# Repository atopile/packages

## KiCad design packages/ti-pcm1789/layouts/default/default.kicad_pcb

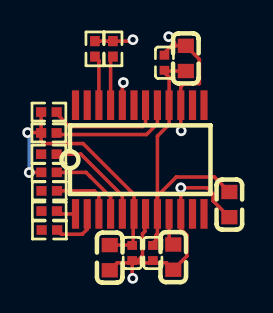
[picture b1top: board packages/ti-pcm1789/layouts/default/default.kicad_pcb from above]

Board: 2 copper layers, 17 parts (0 on the bottom side), 13 nets.

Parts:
C1, C2, C3: 1e-06F; C0402
C4, C5, C6, C7: 9.999F; C0603
R1, R6, R7, R8, R9: 10000Ω; R0402
R2, R3, R4, R5: 22Ω; R0402
U1: TSSOP-24_L7.8-W4.4-P0.65-LS6.4-BL

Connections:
AMUTEI: R6.1, U1.17
BCK: R4.2, U1.2
DIN: R2.2, U1.3
LRCK: R3.2, U1.1
RST: R1.1, U1.4
SCKI: R5.2, U1.5
SCL: R8.1, U1.22
SDA: R9.1, U1.21
ZERO2_AMUTEO: R7.1, U1.18
decoupling_1uf[0]-power-hv: C1.1, C4.1, R1.2, R6.2, R7.2, R8.2, R9.2, U1.6
decoupling_1uf[2]-power-hv: C2.1, C3.1, C5.1, C6.1, U1.8, U1.16
hv: C7.1, U1.9
lv: C1.2, C2.2, C3.2, C4.2, C5.2, C6.2, C7.2, U1.7, U1.10, U1.15, U1.20, U1.23, U1.24

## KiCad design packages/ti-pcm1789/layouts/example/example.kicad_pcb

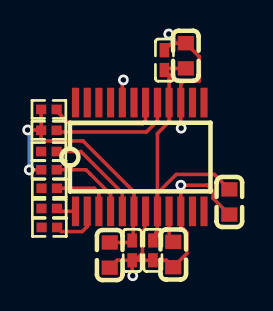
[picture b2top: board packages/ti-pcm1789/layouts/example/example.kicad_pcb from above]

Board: 2 copper layers, 15 parts (0 on the bottom side), 11 nets.

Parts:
C1, C2, C3: 1µF ±10% 25V X5R; C0402
C4, C5, C6, C7: 10µF ±10% 10V X5R; C0603
R1, R2, R3, R4: 22Ω ±1% 62.5mW; R0402
R5, R6, R7: 10kΩ ±1% 62.5mW; R0402
U1: TSSOP-24_L7.8-W4.4-P0.65-LS6.4-BL

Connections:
AMUTEI: R5.1, U1.17
BCK: R3.2, U1.2
DIN: R1.2, U1.3
LRCK: R2.2, U1.1
RST: R6.1, U1.4
SCKI: R4.2, U1.5
VCOM: C7.1, U1.9
ZERO2_AMUTEO: R7.1, U1.18
gnd: C1.2, C2.2, C3.2, C4.2, C5.2, C6.2, C7.2, U1.7, U1.10, U1.15, U1.20
hv: C1.1, C4.1, R5.2, R6.2, R7.2, U1.6
hv-1: C2.1, C3.1, C5.1, C6.1, U1.8, U1.16

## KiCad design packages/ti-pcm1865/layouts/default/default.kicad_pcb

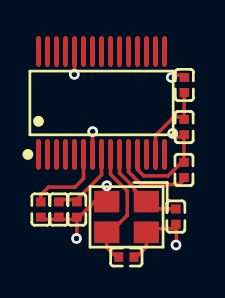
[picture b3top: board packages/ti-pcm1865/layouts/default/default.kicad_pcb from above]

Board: 2 copper layers, 10 parts (0 on the bottom side), 6 nets.

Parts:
C1, C5: 9.999F; C0402
C2, C6: 1F; C0402
C3, C4: 1.2e-F; C0402
C7, C8: 2.2e-F; C0402
U1: TSSOP-30_L7.8-W4.4-P0.50-LS6.4-BL
X1: CRYSTAL-SMD_4P-L3.2-W2.5-BL

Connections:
_power_ldo_cap-power-hv: C7.1, U1.11
_vref_cap-power-hv: C8.1, U1.6
crystal_caps[0]-power-hv: C3.1, U1.10, X1.1
crystal_caps[1]-power-hv: C4.1, U1.9, X1.3
hv: C1.1, C2.1, C5.1, C6.1, U1.8, U1.13, U1.14
lv: C1.2, C2.2, C3.2, C4.2, C5.2, C6.2, C7.2, C8.2, U1.7, U1.12, U1.25, U1.26, X1.2, X1.4

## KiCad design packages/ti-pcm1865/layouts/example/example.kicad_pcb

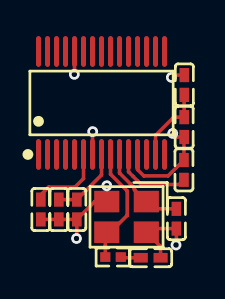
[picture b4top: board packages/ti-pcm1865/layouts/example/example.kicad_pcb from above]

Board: 2 copper layers, 11 parts (0 on the bottom side), 7 nets.

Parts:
C1, C8: 2.2µF ±20% 6.3V X5R; C0402
C2, C6: 10µF ±20% 6.3V X5R; C0402
C3, C7: 100nF ±10% 16V X7R; C0402
C4, C5: 15pF ±5% 50V C0G; C0402
R1: 0Ω 62.5mW; R0402
U1: TSSOP-30_L7.8-W4.4-P0.50-LS6.4-BL
X1: CRYSTAL-SMD_4P-L3.2-W2.5-BL

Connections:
LDO: C1.1, U1.11
VREF: C8.1, U1.6
XI: C5.1, U1.10, X1.1
XO: R1.2, U1.9, X1.3
gnd: C1.2, C2.2, C3.2, C4.2, C5.2, C6.2, C7.2, C8.2, U1.7, U1.12, U1.26, X1.2, X1.4
hv: C2.1, C3.1, C6.1, C7.1, U1.8, U1.13, U1.14
net: C4.1, R1.1

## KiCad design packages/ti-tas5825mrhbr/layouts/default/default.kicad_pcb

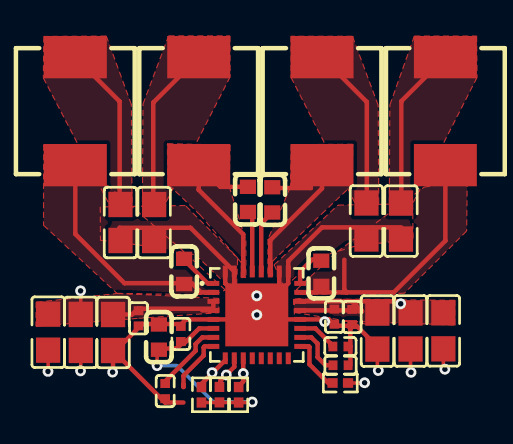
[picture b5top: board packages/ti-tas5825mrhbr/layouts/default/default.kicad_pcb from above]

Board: 2 copper layers, 31 parts (0 on the bottom side), 22 nets.

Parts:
C1, C2, C12, C19, C20, C21, C22: 0F; C0402
C3, C4, C7, C8, C11: 0F; C0603
C5, C6, C9, C10, C13, C14, C15, C16, C17, C18: 0F; C0805
L1, L2, L3, L4: L 0H; IND-SMD_L7.3-W6.8
R2, R3, R4, R5: 10000Ω; R0402
U1: VQFN-32_L5.0-W5.0-P0.50-TL-EP

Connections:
9: R2.1, U1.9
10: R3.1, U1.10
11: R5.1, U1.11
avdd_cap-power-hv: C1.1, U1.19
bootstrap_N: C7.1, U1.28
bootstrap_P: C4.1, U1.1
bootstrap_neg-power-bootstrap_N: C3.1, U1.29
bootstrap_neg-power-lv_N: C3.2, L1.1, U1.30
bootstrap_pos-power-bootstrap_P: C8.1, U1.24
bootstrap_pos-power-lv_P: C8.2, L4.1, U1.23
hv: C2.1, U1.18
lv: C1.2, C2.2, C5.2, C6.2, C9.2, C10.2, C11.2, C12.2, C13.2, C14.2, C15.2, C16.2, C17.2, C18.2, C19.2, C20.2, C21.2, C22.2, U1.5, U1.20, U1.25, U1.26, U1.31, U1.32, U1.33
lv_N: C7.2, L3.1, U1.27
lv_P: C4.2, L2.1, U1.2
nPDN: R4.1, U1.17
output_a_N: C5.1, L1.2
output_a_P: C6.1, L2.2
output_b_N: C9.1, L3.2
output_b_P: C10.1, L4.2
pvdd_caps[8]-power-hv: C13.1, C14.1, C15.1, C16.1, C17.1, C18.1, C20.1, C21.1, C22.1, U1.3, U1.4, U1.21, U1.22
reference-hv: C11.1, C12.1, R2.2, R3.2, R4.2, R5.2, U1.6
vr_dig_cap-power-hv: C19.1, U1.7
